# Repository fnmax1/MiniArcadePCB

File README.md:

# MiniArcade
This repository provides a complete kit for a handheld console
in the form of an arcade machine.

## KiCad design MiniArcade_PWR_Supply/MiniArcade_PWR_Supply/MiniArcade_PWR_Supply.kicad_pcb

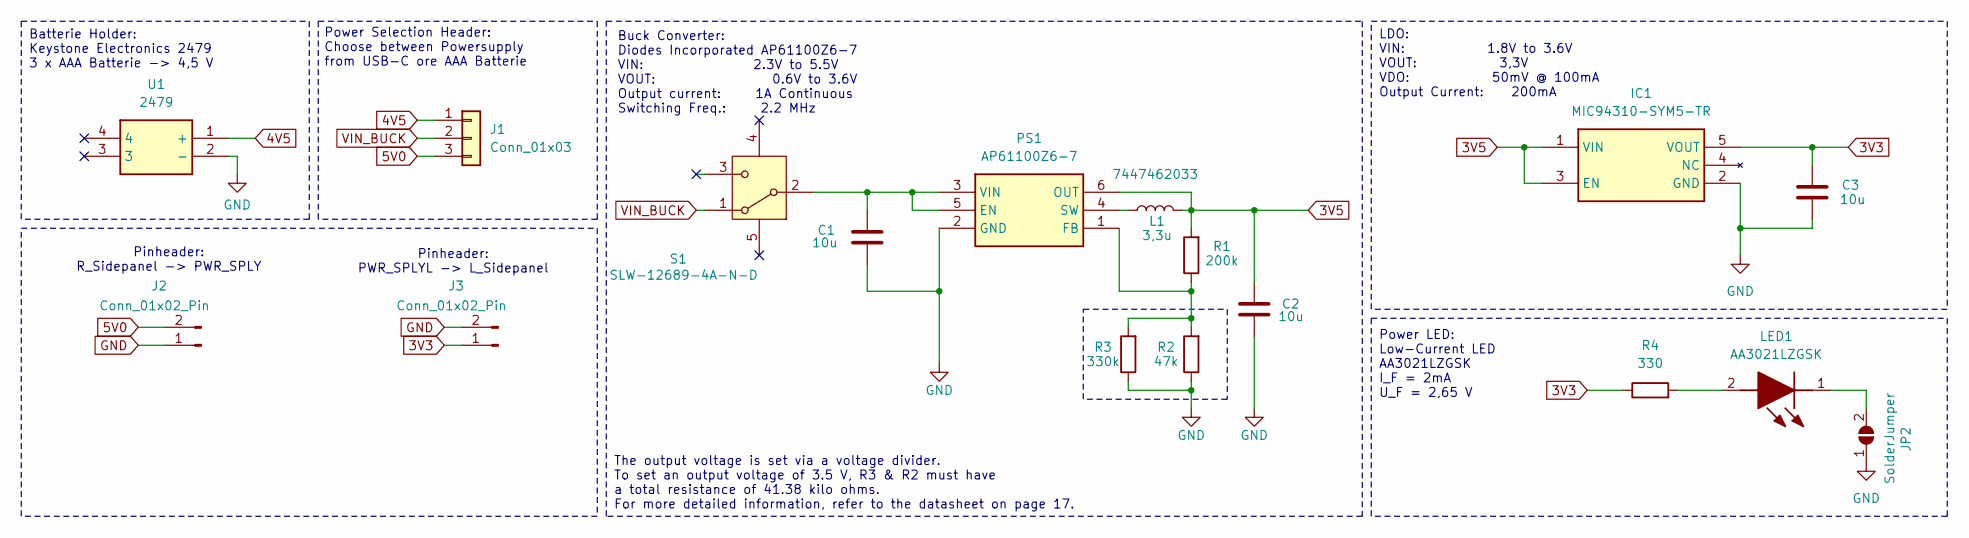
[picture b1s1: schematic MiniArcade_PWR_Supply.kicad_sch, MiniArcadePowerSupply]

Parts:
C1, C2, C3: 10u; C_0805_2012Metric_Pad1.18x1.45mm_HandSolder
IC1: MIC94310-SYM5-TR; SOT95P280X130-5N; Mouser Part Number 998-MIC94310-SYM5TR
J1: Conn_01x03; PinHeader_1x03_P1.00mm_Vertical
J2, J3: Conn_01x02_Pin; PinHeader_1x02_P2.54mm_Vertical
JP2: SolderJumper; SolderJumper-2_P1.3mm_Open_Pad1.0x1.5mm
L1: 3,3u; WE-TI_507589
LED1: AA3021LZGSK; LEDM3020X150N; Mouser Part Number 604-AA3021LZGSK
PS1: AP61100Z6-7; SOT50P162X60-6N; Mouser Part Number 621-AP61100Z6-7
R1: 200k; R_0805_2012Metric_Pad1.20x1.40mm_HandSolder
R2: 47k; R_0805_2012Metric_Pad1.20x1.40mm_HandSolder
R3: 330k; R_0805_2012Metric_Pad1.20x1.40mm_HandSolder
R4: 330; R_0603_1608Metric_Pad0.98x0.95mm_HandSolder
S1: SLW-12689-4A-N-D; SLW126894AND; Mouser Part Number 179-SLW126894AND
U1: 2479; Mouser Part Number 534-2479

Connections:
3V3: C3.1, IC1.5 (VOUT), J3.1, R4.1
3V5: C2.1, IC1.1 (VIN), IC1.3 (EN), L1.2, PS1.6 (OUT), R1.2
4V5: J1.1, U1.1 (+)
5V0: J1.3, J2.2
GND: C1.2, C2.2, C3.2, IC1.2 (GND), J2.1, J3.2, JP2.1 (A), PS1.2 (GND), R2.1, R3.1, U1.2 (-)
unnamed: JP2.2 (B), LED1.1 (K)
unnamed: LED1.2 (A), R4.2
unnamed: C1.1, PS1.3 (VIN), PS1.5 (EN), S1.2
unnamed: PS1.1 (FB), R1.1, R2.2, R3.2
unnamed: L1.1, PS1.4 (SW)
VIN_BUCK: J1.2, S1.1

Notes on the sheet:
Pinheader: R_Sidepanel -> PWR_SPLY
Batterie Holder: Keystone Electronics 2479 3 x AAA Batterie -> 4,5 V
Power Selection Header: Choose between Powersupply from USB-C ore AAA Batterie
Pinheader: PWR_SPLYL -> L_Sidepanel
The output voltage is set via a voltage divider. To set an output voltage of 3.5 V, R3 & R2 must have a total resistance of 41.38 kilo ohms. For more detailed information, refer to the datasheet on page 17.
Power LED: Low-Current LED AA3021LZGSK I_F = 2mA U_F = 2,65 V
Buck Converter: Diodes Incorporated AP61100Z6-7 VIN: 2.3V to 5.5V VOUT: 0.6V to 3.6V Output current: 1A Continuous Switching Freq.: 2.2 MHz
LDO: VIN: 1.8V to 3.6V VOUT: 3,3V VDO: 50mV @ 100mA Output Current: 200mA

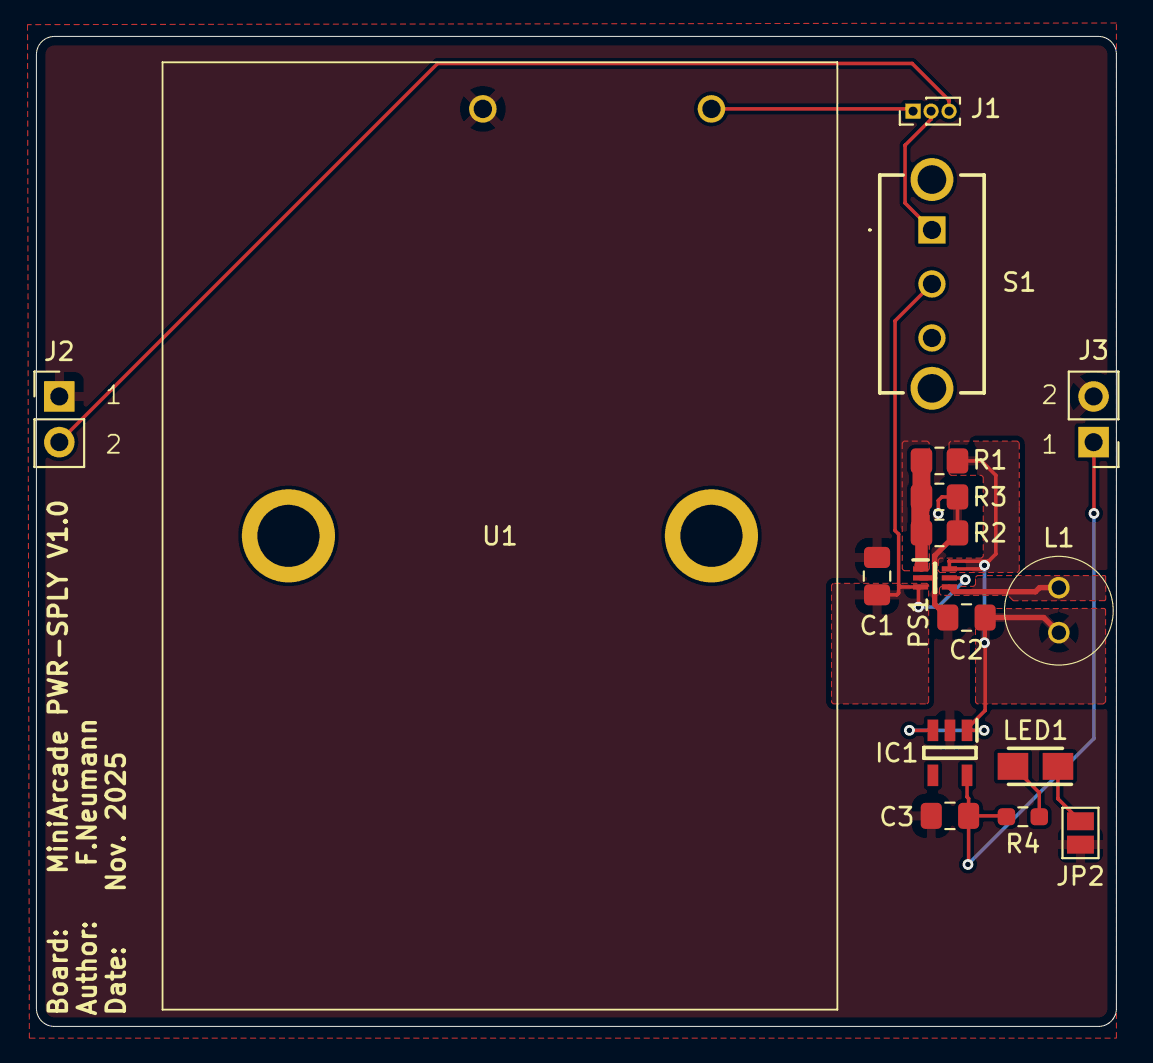
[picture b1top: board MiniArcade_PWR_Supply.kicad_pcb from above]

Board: 2 copper layers, 60.0 x 55.0 mm, 17 parts (0 on the bottom side), 11 nets.

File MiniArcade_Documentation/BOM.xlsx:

Funktion | Hersteller Bez. | Kosten in € | Anzahl | Website
Main Board
J-Tag Header | 62701021721 | 1.56 | 1 | https://www.mouser.de/ProductDetail/Wurth-Elektronik/6270102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
Mikrokonroller | SAMD21J18A-A
User LED | AA3021LZGSK | 0.46 | 1 | https://www.mouser.de/ProductDetail/Kingbright/AA3021LZGSK?q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
Ferrit Bead | 742792022 | 0.2 | 1 | https://www.mouser.de/ProductDetail/Wurth-Elektronik/7427920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
Piezo Buzzer | CPT-1207-3TH | 0.43 | 1 | https://www.mouser.de/ProductDetail/Same-Sky/CPT-1207-3TH?qs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
OpAmp | LM321LVIDBVR | 0.11 | 1 | https://www.mouser.de/ProductDetail/Texas-Instruments/LM321L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
LCD | ER-TFT1.44-1 | 2.42 | 1 | https://www.buydisplay.com/1-44-inch-tft-touch-screen-serial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
FPC-Connector | F3311A7H121026E200 | 0.34 | 1 | https://www.mouser.de/ProductDetail/Amphenol-Aorora/F3311A7H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
Power Supply
Buck Converter | AP61100Z6-7 | 0.17 | 1 | https://www.mouser.de/ProductDetail/Diodes-Incorporated/AP61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
Power LED | AA3021LZGSK | 0.46 | 1 | https://www.mouser.de/ProductDetail/Kingbright/AA3021LZGSK?q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
LDO | MIC94310-SYM5-TR | 0.27 | 1 | https://www.mouser.de/ProductDetail/Microchip-Technology/MIC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
Power-Switch | SLW-12689-4A-N-D | 0.28999999999999998 | 1 | https://www.mouser.de/ProductDetail/Same-Sky/SLW-12689-4A-N-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
Induktivität 2,2 uH | 7447462022 | 0.82 | 1 | https://www.mouser.de/ProductDetail/Wurth-Elektronik/7447462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
Induktivität 3,3 uH | 7447462033 | 0.82 | 1 | https://www.mouser.de/ProductDetail/Wurth-Elektronik/7447462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
Induktivität 4,7 uH | 7447462047 | 0.82 | 1 | https://www.mouser.de/ProductDetail/Wurth-Elektronik/7447462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
Batterie Holder | 2479 | 1.26 | 1 | https://www.mouser.de/ProductDetail/Keystone-Electronics/247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
Controller
Joystick | 10*10*9-6P WX | 0.37 | 1 | https://www.lcsc.com/product-detail/C2858290.html
Left Side Panel
PinHeader_1x2_female_90° | M20-7910242R | 0.61 | 1 | https://www.mouser.de/ProductDetail/Harwin/M20-7910242R?qs=k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
PinHeader_1x5_female_90° | M20-7910542R | 0.91 | 1 | https://www.mouser.de/ProductDetail/Harwin/M20-7910542R?qs=k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
PinHeader_1x6_female_90° | M20-7910642R | 1.0900000000000001 | 1 | https://www.mouser.de/ProductDetail/Harwin/M20-7910642R?qs=k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
Right Side Panel
PinHeader_1x2_female_90° | M20-7910242R | 0.61 | 1 | https://www.mouser.de/ProductDetail/Harwin/M20-7910242R?qs=k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
PinHeader_1x5_female_90° | M20-7910542R | 0.91 | 2 | https://www.mouser.de/ProductDetail/Harwin/M20-7910542R?qs=k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
USB-C | USB4125-GF-A | 0.51 | 1 | https://www.mouser.de/ProductDetail/GCT/USB4125-GF-A?qs=KUoI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

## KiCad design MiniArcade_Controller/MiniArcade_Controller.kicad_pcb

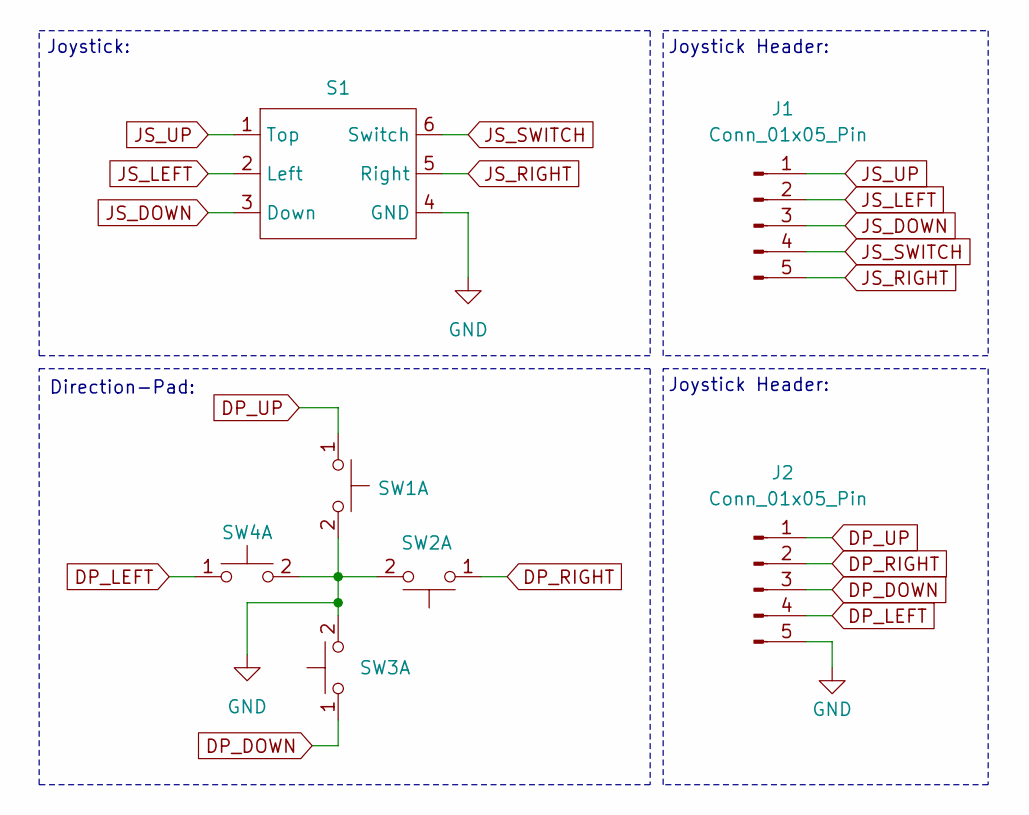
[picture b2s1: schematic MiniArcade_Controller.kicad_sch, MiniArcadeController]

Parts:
J1, J2: Conn_01x05_Pin; PinHeader_1x05_P2.54mm_Vertical
S1: Joystick
SW1, SW2, SW3, SW4: SW_Push_Dual_x2; SW_PUSH_6mm_H5mm

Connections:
DP_DOWN: J2.3, SW3.1 (C)
DP_LEFT: J2.4, SW4.1 (C)
DP_RIGHT: J2.2, SW2.1 (C)
DP_UP: J2.1, SW1.1 (C)
GND: J2.5, S1.4 (GND), SW1.2 (D), SW2.2 (D), SW3.2 (D), SW4.2 (D)
JS_DOWN: J1.3, S1.3 (Down)
JS_LEFT: J1.2, S1.2 (Left)
JS_RIGHT: J1.5, S1.5 (Right)
JS_SWITCH: J1.4, S1.6 (Switch)
JS_UP: J1.1, S1.1 (Top)

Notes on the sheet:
Joystick Header:
Direction-Pad:
Joystick:

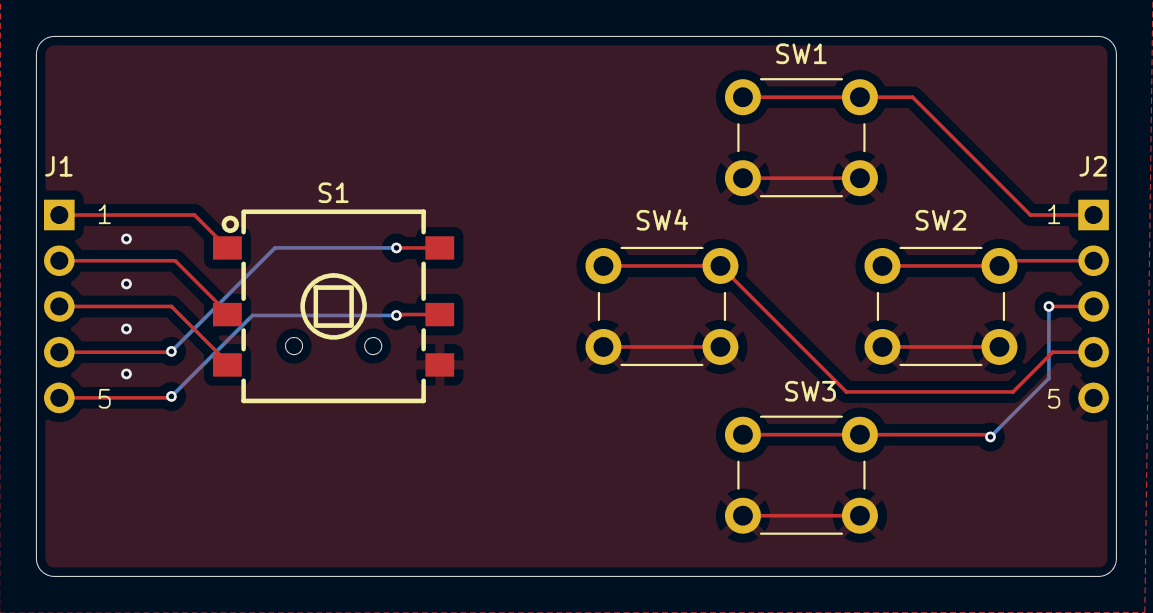
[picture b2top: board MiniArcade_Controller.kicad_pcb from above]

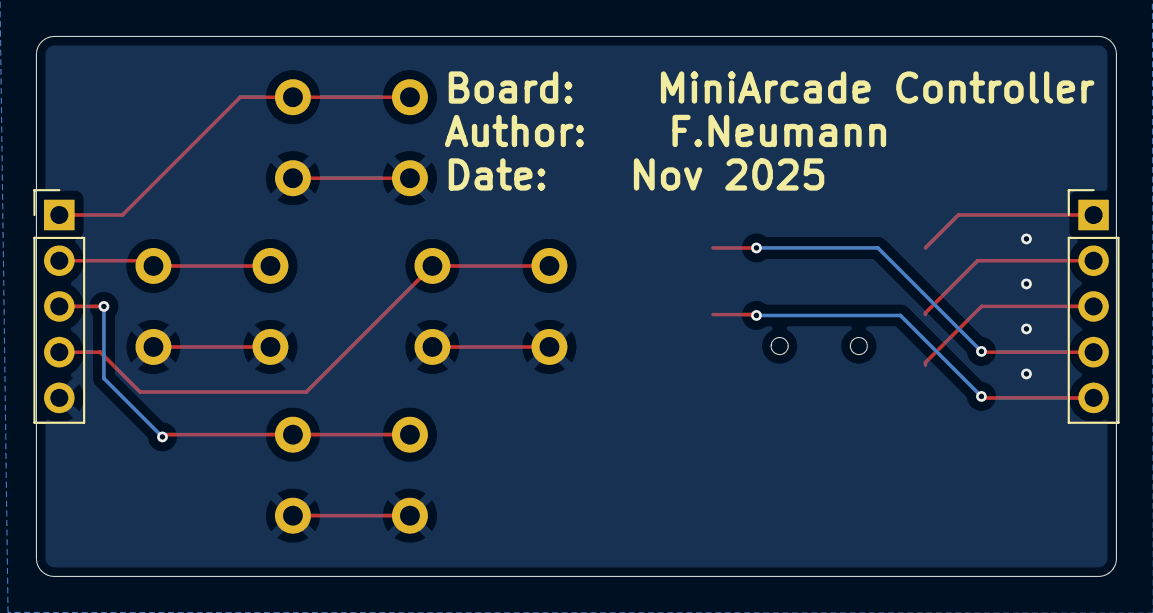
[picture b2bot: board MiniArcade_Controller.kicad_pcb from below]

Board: 2 copper layers, 60.0 x 30.0 mm, 7 parts (2 on the bottom side), 10 nets.

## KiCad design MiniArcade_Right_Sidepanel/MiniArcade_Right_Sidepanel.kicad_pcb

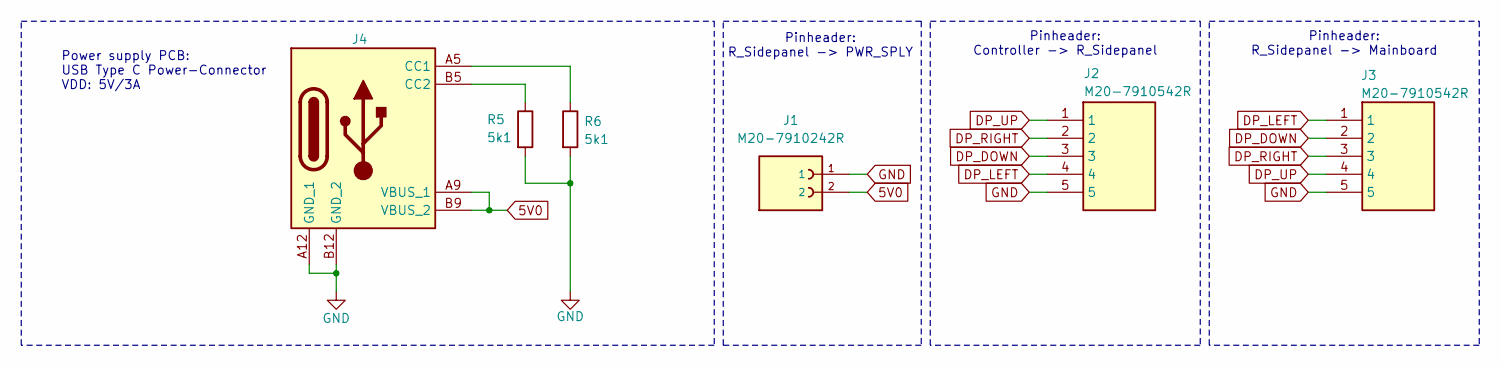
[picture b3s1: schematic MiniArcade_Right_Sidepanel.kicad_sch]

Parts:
J1: M20-7910242R; HARWIN_M20-7910242R; PARTREV 3
J2, J3: M20-7910542R; M207910542R; Mouser Part Number 855-M20-7910542R
J4: USB4125GFA
R5, R6: 5k1; R_0603_1608Metric_Pad0.98x0.95mm_HandSolder

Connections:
5V0: J1.2, J4.A9 (VBUS_1), J4.B9 (VBUS_2)
DP_DOWN: J2.3, J3.2
DP_LEFT: J2.4, J3.1
DP_RIGHT: J2.2, J3.3
DP_UP: J2.1, J3.4
GND: J1.1, J2.5, J3.5, J4.A12 (GND_1), J4.B12 (GND_2), R5.2, R6.2
unnamed: J4.A5 (CC1), R6.1
unnamed: J4.B5 (CC2), R5.1

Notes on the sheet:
Pinheader: R_Sidepanel -> Mainboard
Power supply PCB: USB Type C Power-Connector VDD: 5V/3A
Pinheader: Controller -> R_Sidepanel
Pinheader: R_Sidepanel -> PWR_SPLY

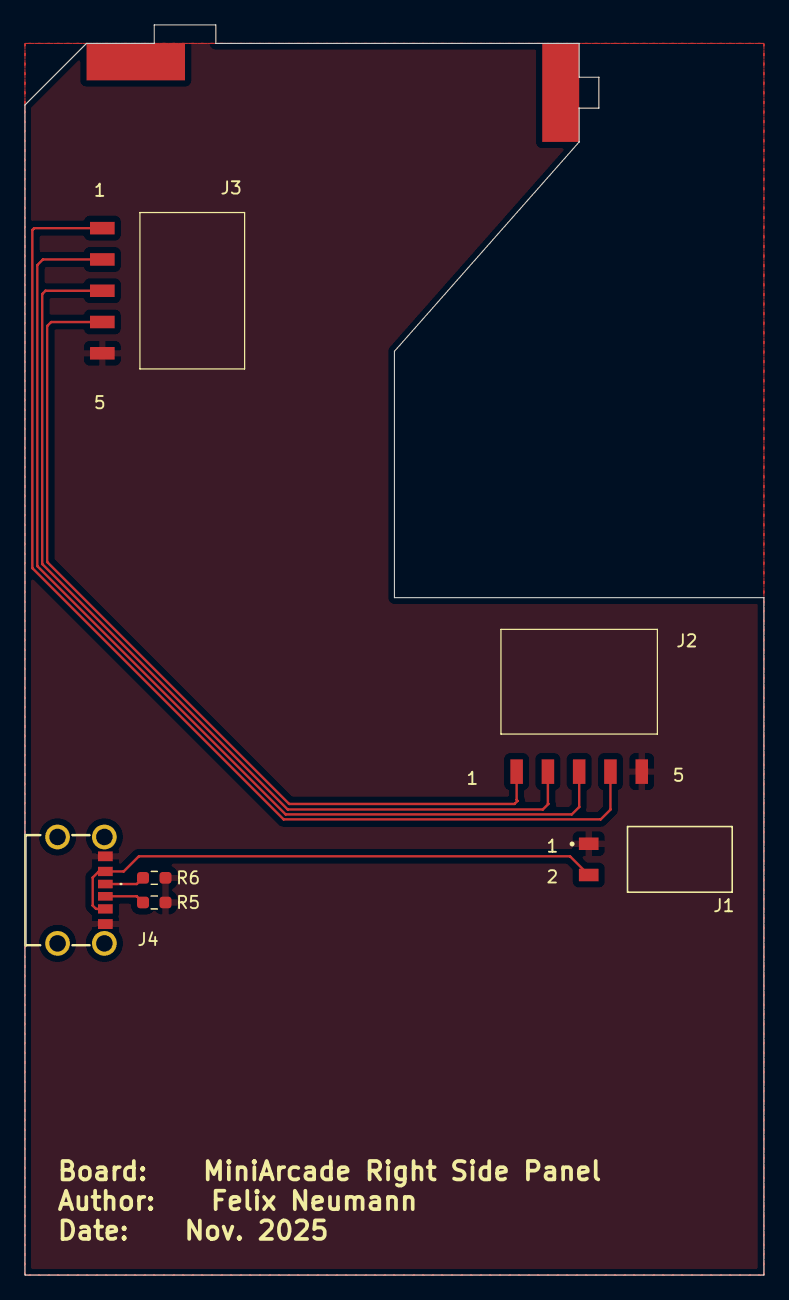
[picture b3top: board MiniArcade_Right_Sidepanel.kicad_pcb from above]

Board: 2 copper layers, 60.0 x 101.5 mm, 6 parts (0 on the bottom side), 8 nets.

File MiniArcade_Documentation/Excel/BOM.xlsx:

Funktion | Hersteller Bez. | Kosten in € | Anzahl |  | Website
Main Board
J-Tag Header | 62701021721 | 1.56 | 1 |  | https://www.mouser.de/ProductDetail/Wurth-Elektronik/6270102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
Mikrokonroller | SAMD21J18A-A
User LED | AA3021LZGSK | 0.46 | 1 |  | https://www.mouser.de/ProductDetail/Kingbright/AA3021LZGSK?q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
Ferrit Bead | 742792022 | 0.2 | 1 |  | https://www.mouser.de/ProductDetail/Wurth-Elektronik/7427920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
Piezo Buzzer | CPT-1207-3TH | 0.43 | 1 |  | https://www.mouser.de/ProductDetail/Same-Sky/CPT-1207-3TH?qs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
OpAmp | LM321LVIDBVR | 0.11 | 1 |  | https://www.mouser.de/ProductDetail/Texas-Instruments/LM321L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
LCD | ER-TFT1.44-1 | 2.42 | 1 | ??? | https://www.buydisplay.com/1-44-inch-tft-touch-screen-serial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
FPC-Connector | F3311A7H121026E200 | 0.34 | 1 |  | https://www.mouser.de/ProductDetail/Amphenol-Aorora/F3311A7H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
Power Supply
Buck Converter | AP61100Z6-7 | 0.17 | 1 |  | https://www.mouser.de/ProductDetail/Diodes-Incorporated/AP61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
Power LED | AA3021LZGSK | 0.46 | 1 |  | https://www.mouser.de/ProductDetail/Kingbright/AA3021LZGSK?q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
LDO | MIC94310-SYM5-TR | 0.27 | 1 |  | https://www.mouser.de/ProductDetail/Microchip-Technology/MIC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
Power-Switch | SLW-12689-4A-N-D | 0.28999999999999998 | 1 |  | https://www.mouser.de/ProductDetail/Same-Sky/SLW-12689-4A-N-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
Induktivität 2,2 uH | 7447462022 | 0.82 | 1 |  | https://www.mouser.de/ProductDetail/Wurth-Elektronik/7447462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
Induktivität 3,3 uH | 7447462033 | 0.82 | 1 |  | https://www.mouser.de/ProductDetail/Wurth-Elektronik/7447462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
Induktivität 4,7 uH | 7447462047 | 0.82 | 1 |  | https://www.mouser.de/ProductDetail/Wurth-Elektronik/7447462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
Batterie Holder | 2479 | 1.26 | 1 |  | https://www.mouser.de/ProductDetail/Keystone-Electronics/247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
Controller
Joystick | 10*10*9-6P WX | 0.37 | 1 |  | https://www.lcsc.com/product-detail/C2858290.html
Left Side Panel
PinHeader_1x2_female_90° | M20-7910242R | 0.61 | 1 |  | https://www.mouser.de/ProductDetail/Harwin/M20-7910242R?qs=k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
PinHeader_1x5_female_90° | M20-7910542R | 0.91 | 1 |  | https://www.mouser.de/ProductDetail/Harwin/M20-7910542R?qs=k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
PinHeader_1x6_female_90° | M20-7910642R | 1.0900000000000001 | 1 |  | https://www.mouser.de/ProductDetail/Harwin/M20-7910642R?qs=k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
Right Side Panel
PinHeader_1x2_female_90° | M20-7910242R | 0.61 | 1 |  | https://www.mouser.de/ProductDetail/Harwin/M20-7910242R?qs=k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
PinHeader_1x5_female_90° | M20-7910542R | 0.91 | 2 |  | https://www.mouser.de/ProductDetail/Harwin/M20-7910542R?qs=k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
USB-C | USB4125-GF-A | 0.51 | 1 |  | https://www.mouser.de/ProductDetail/GCT/USB4125-GF-A?qs=KUoI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

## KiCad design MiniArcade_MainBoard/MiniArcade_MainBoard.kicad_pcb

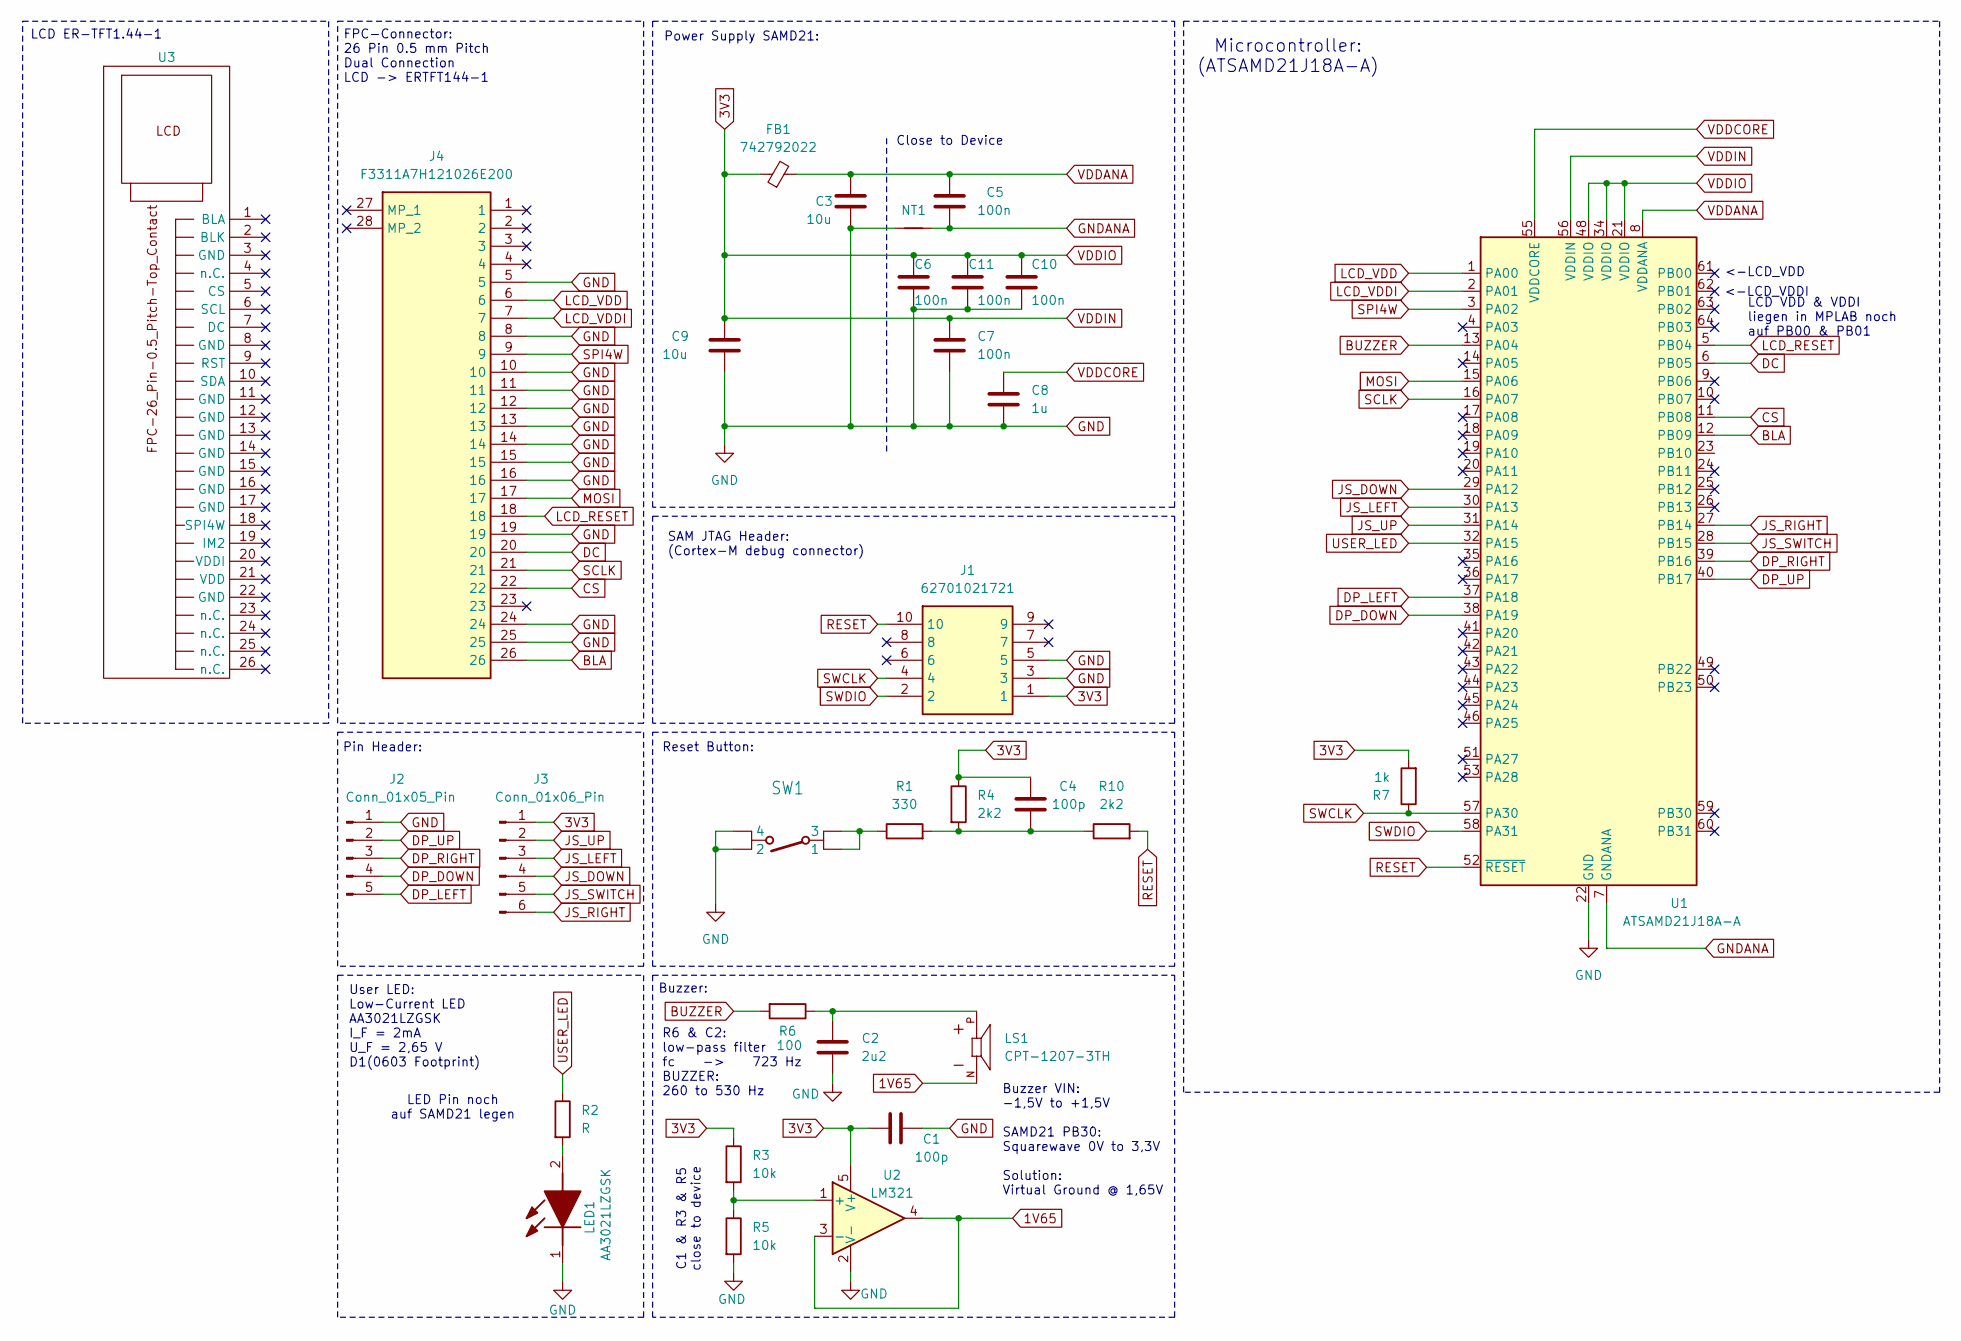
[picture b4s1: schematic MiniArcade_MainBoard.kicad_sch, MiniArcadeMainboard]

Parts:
C1, C4: 100p; C_0805_2012Metric_Pad1.18x1.45mm_HandSolder
C2: 2u2; C_0805_2012Metric_Pad1.18x1.45mm_HandSolder
C3, C9: 10u; C_0805_2012Metric_Pad1.18x1.45mm_HandSolder
C5, C6, C7, C10, C11: 100n; C_0805_2012Metric_Pad1.18x1.45mm_HandSolder
C8: 1u; C_0805_2012Metric_Pad1.18x1.45mm_HandSolder
FB1: 742792022; R_0805_2012Metric_Pad1.20x1.40mm_HandSolder; Mouser Part Number 710-742792022
J1: 62701021721; Manufacturer_Part_Number 62701021721
J2: Conn_01x05_Pin; PinHeader_1x05_P2.54mm_Vertical
J3: Conn_01x06_Pin; PinHeader_1x06_P2.54mm_Vertical
J4: F3311A7H121026E200; Mouser Part Number 649-311A7H121026E200
LED1: AA3021LZGSK; LEDM3020X150N; Mouser Part Number 604-AA3021LZGSK
LS1: CPT-1207-3TH; SPKR_CPT-1207-3TH; PARTREV 1.0
NT1: NetTie_2; NetTie-2_SMD_Pad0.5mm
R1: 330; R_0805_2012Metric_Pad1.20x1.40mm_HandSolder
R2: R; R_0805_2012Metric_Pad1.20x1.40mm_HandSolder
R3, R5: 10k; R_0805_2012Metric_Pad1.20x1.40mm_HandSolder
R4, R10: 2k2; R_0805_2012Metric_Pad1.20x1.40mm_HandSolder
R6: 100; R_0805_2012Metric_Pad1.20x1.40mm_HandSolder
R7: 1k; R_0805_2012Metric_Pad1.20x1.40mm_HandSolder
SW1: EVPAA
U1: ATSAMD21J18A-A; TQFP-64_10x10mm_P0.5mm
U2: LM321; SOT95P280X145-5N
U3: ERTFT144

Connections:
1V65: LS1.N, U2.3 (-), U2.4
3V3: C1.1, C4.1, C6.1, C7.1, C9.1, C10.1, C11.1, FB1.1, J1.1, J3.1, R3.1, R4.1, R7.2, U1.21 (VDDIO), U1.34 (VDDIO), U1.48 (VDDIO), U1.56 (VDDIN), U2.5 (V+)
BLA: J4.26, U1.12 (PB09)
BUZZER: R6.2, U1.13 (PA04)
CS: J4.22, U1.11 (PB08)
DC: J4.20, U1.6 (PB05)
DP_DOWN: J2.4, U1.38 (PA19)
DP_LEFT: J2.5, U1.37 (PA18)
DP_RIGHT: J2.3, U1.39 (PB16)
DP_UP: J2.2, U1.40 (PB17)
GND: C1.2, C2.1, C3.2, C6.2, C7.2, C8.2, C9.2, C10.2, C11.2, J1.3, J1.5, J2.1, J4.5, J4.8, J4.10, J4.11, J4.12, J4.13, J4.14, J4.15, J4.16, J4.19, J4.24, J4.25, LED1.1 (K), NT1.1, R5.2, SW1.2, SW1.4, U1.22 (GND), U1.33 (GND), U1.47 (GND), U1.54 (GND), U2.2 (V-)
GNDANA: C5.2, NT1.2, U1.7 (GNDANA)
JS_DOWN: J3.4, U1.29 (PA12)
JS_LEFT: J3.3, U1.30 (PA13)
JS_RIGHT: J3.6, U1.27 (PB14)
JS_SWITCH: J3.5, U1.28 (PB15)
JS_UP: J3.2, U1.31 (PA14)
LCD_RESET: J4.18, U1.5 (PB04)
LCD_VDD: J4.6, U1.1 (PA00)
LCD_VDDI: J4.7, U1.2 (PA01)
MOSI: J4.17, U1.15 (PA06)
unnamed: C2.2, LS1.P, R6.1
unnamed: C4.2, R1.2, R4.2, R10.1
unnamed: LED1.2 (A), R2.2
unnamed: R1.1, SW1.1, SW1.3
unnamed: R3.2, R5.1, U2.1 (+)
RESET: J1.10, R10.2, U1.52 (~RESET)
SCLK: J4.21, U1.16 (PA07)
SPI4W: J4.9, U1.3 (PA02)
SWCLK: J1.4, R7.1, U1.57 (PA30)
SWDIO: J1.2, U1.58 (PA31)
USER_LED: R2.1, U1.32 (PA15)
VDDANA: C3.1, C5.1, FB1.2, U1.8 (VDDANA)
VDDCORE: C8.1, U1.55 (VDDCORE)

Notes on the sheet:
Power Supply SAMD21:
LCD VDD & VDDI liegen in MPLAB noch auf PB00 & PB01
SAM JTAG Header: (Cortex-M debug connector)
Buzzer:
User LED: Low-Current LED AA3021LZGSK I_F = 2mA U_F = 2,65 V D1(0603 Footprint)
LCD ER-TFT1.44-1
LED Pin noch auf SAMD21 legen
Reset Button:
<-LCD_VDD
Microcontroller: (ATSAMD21J18A-A)
Pin Header:
R6 & C2: low-pass filter fc -> 723 Hz BUZZER: 260 to 530 Hz
FPC-Connector: 26 Pin 0.5 mm Pitch Dual Connection LCD -> ERTFT144-1
Close to Device
Buzzer VIN: -1,5V to +1,5V SAMD21 PB30: Squarewave 0V to 3,3V Solution: Virtual Ground @ 1,65V
<-LCD_VDDI
C1 & R3 & R5 close to device

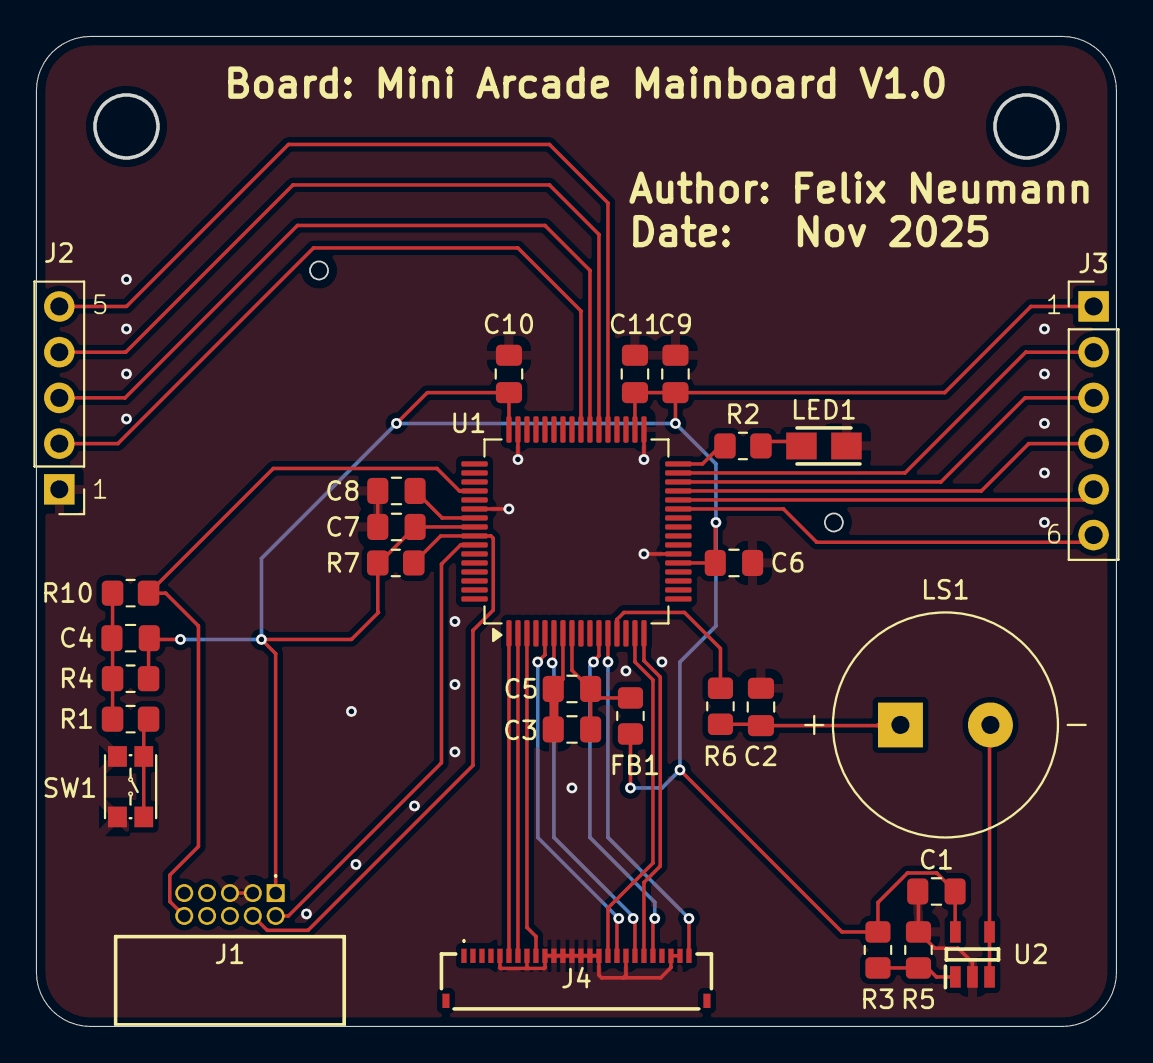
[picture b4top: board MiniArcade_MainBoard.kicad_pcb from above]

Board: 2 copper layers, 60.0 x 55.0 mm, 31 parts (1 on the bottom side), 34 nets.

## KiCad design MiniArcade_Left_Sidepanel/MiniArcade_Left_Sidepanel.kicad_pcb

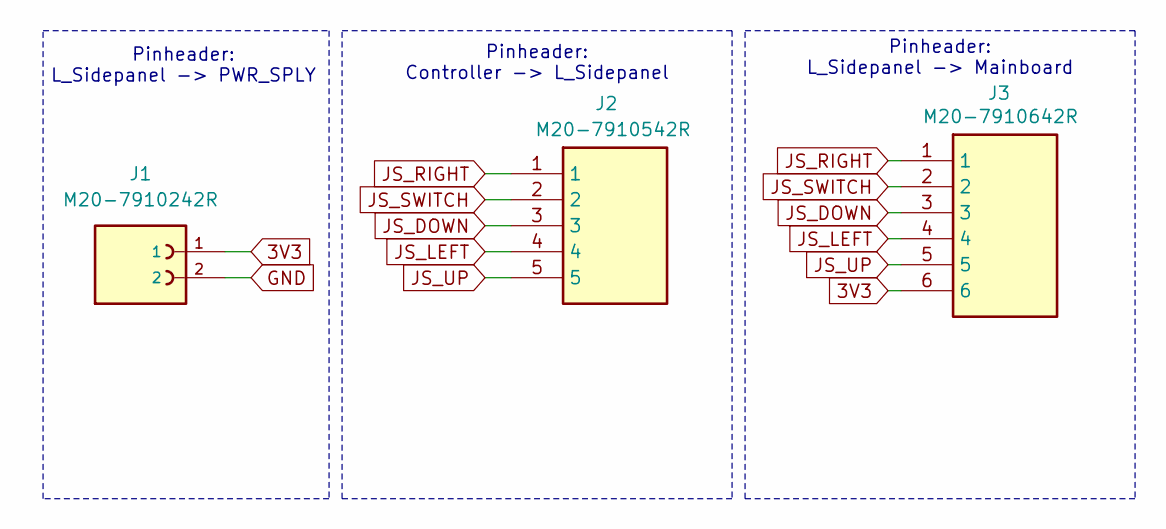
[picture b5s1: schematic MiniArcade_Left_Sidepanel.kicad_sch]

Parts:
J1: M20-7910242R; HARWIN_M20-7910242R; PARTREV 3
J2: M20-7910542R; M207910542R; Mouser Part Number 855-M20-7910542R
J3: M20-7910642R; M207910642R; Mouser Part Number 855-M20-7910642R

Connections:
3V3: J1.1, J3.6
GND: J1.2
JS_DOWN: J2.3, J3.3
JS_LEFT: J2.4, J3.4
JS_RIGHT: J2.1, J3.1
JS_SWITCH: J2.2, J3.2
JS_UP: J2.5, J3.5

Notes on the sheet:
Pinheader: Controller -> L_Sidepanel
Pinheader: L_Sidepanel -> PWR_SPLY
Pinheader: L_Sidepanel -> Mainboard

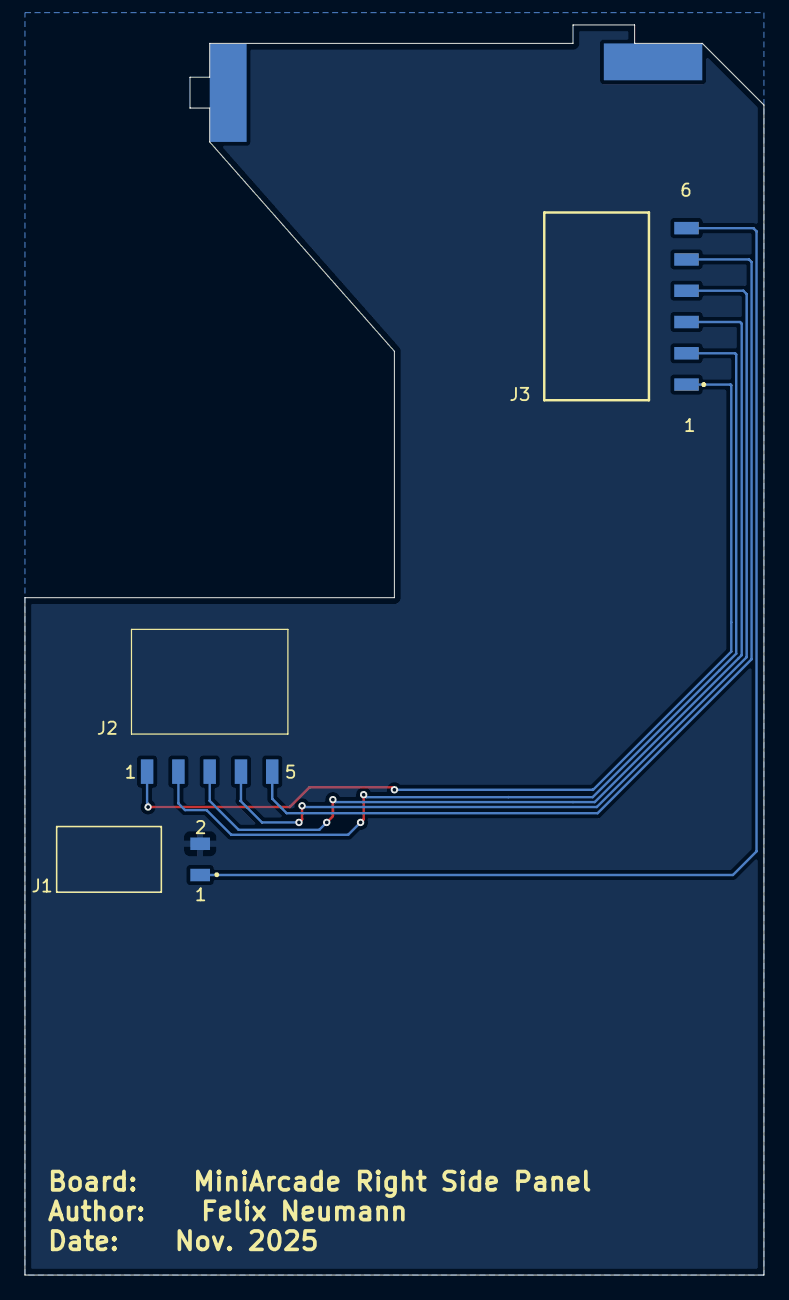
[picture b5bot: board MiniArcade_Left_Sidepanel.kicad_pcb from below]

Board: 2 copper layers, 60.0 x 101.5 mm, 3 parts (3 on the bottom side), 6 nets.

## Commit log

2025-10-27 MiniArcadeController 27102025
2025-10-28 dateiein aus repository entfernt
2025-10-28 MiniArcadeController Initial Commit
2025-10-28 MiniArcadePowerSupply Initial Commit
2025-10-28 MiniArcade Mainboard Initial Commit
2025-10-29 deleted
2025-10-29 added author and title to shemaitc
2025-10-29 MiniArcade MainBoard & Power Supply initial commit
2025-10-29 title and Author added
2025-10-29 test
2025-11-03 stand 03 11
2025-11-04 stand 04 11 2025
2025-11-05 05 11 2025
2025-11-10 10 11 2025
2025-11-11 11 11 2025
2025-11-12 12 11 2025
2025-11-14 14 11 2025
2025-11-17 17 11 2025
2025-11-19 19 11 2025
2025-11-21 21 11 2025
2025-11-25 25 11 2025
2025-11-26 26 11 2025
2025-12-08 08 12 2025
2025-12-30 30.12.2025
2026-01-04 04 01 26
2026-01-09 09 01 26
2026-01-12 12 01 26
2026-01-13 13 01 2026
2026-01-13 13 01 26
2026-01-29 29 01 2026
2026-01-31 31 01 2026
2026-02-02 02 02 2026
2026-02-03 03 02 2026
2026-02-04 04 02 2026
2026-02-06 06 02 2026
2026-02-10 10 02 2026
2026-02-16 16 02 26
2026-02-17 17 02 2026
2026-02-18 18 02 2026
2026-02-19 19 02 2026
2026-02-23 23 02 2026
